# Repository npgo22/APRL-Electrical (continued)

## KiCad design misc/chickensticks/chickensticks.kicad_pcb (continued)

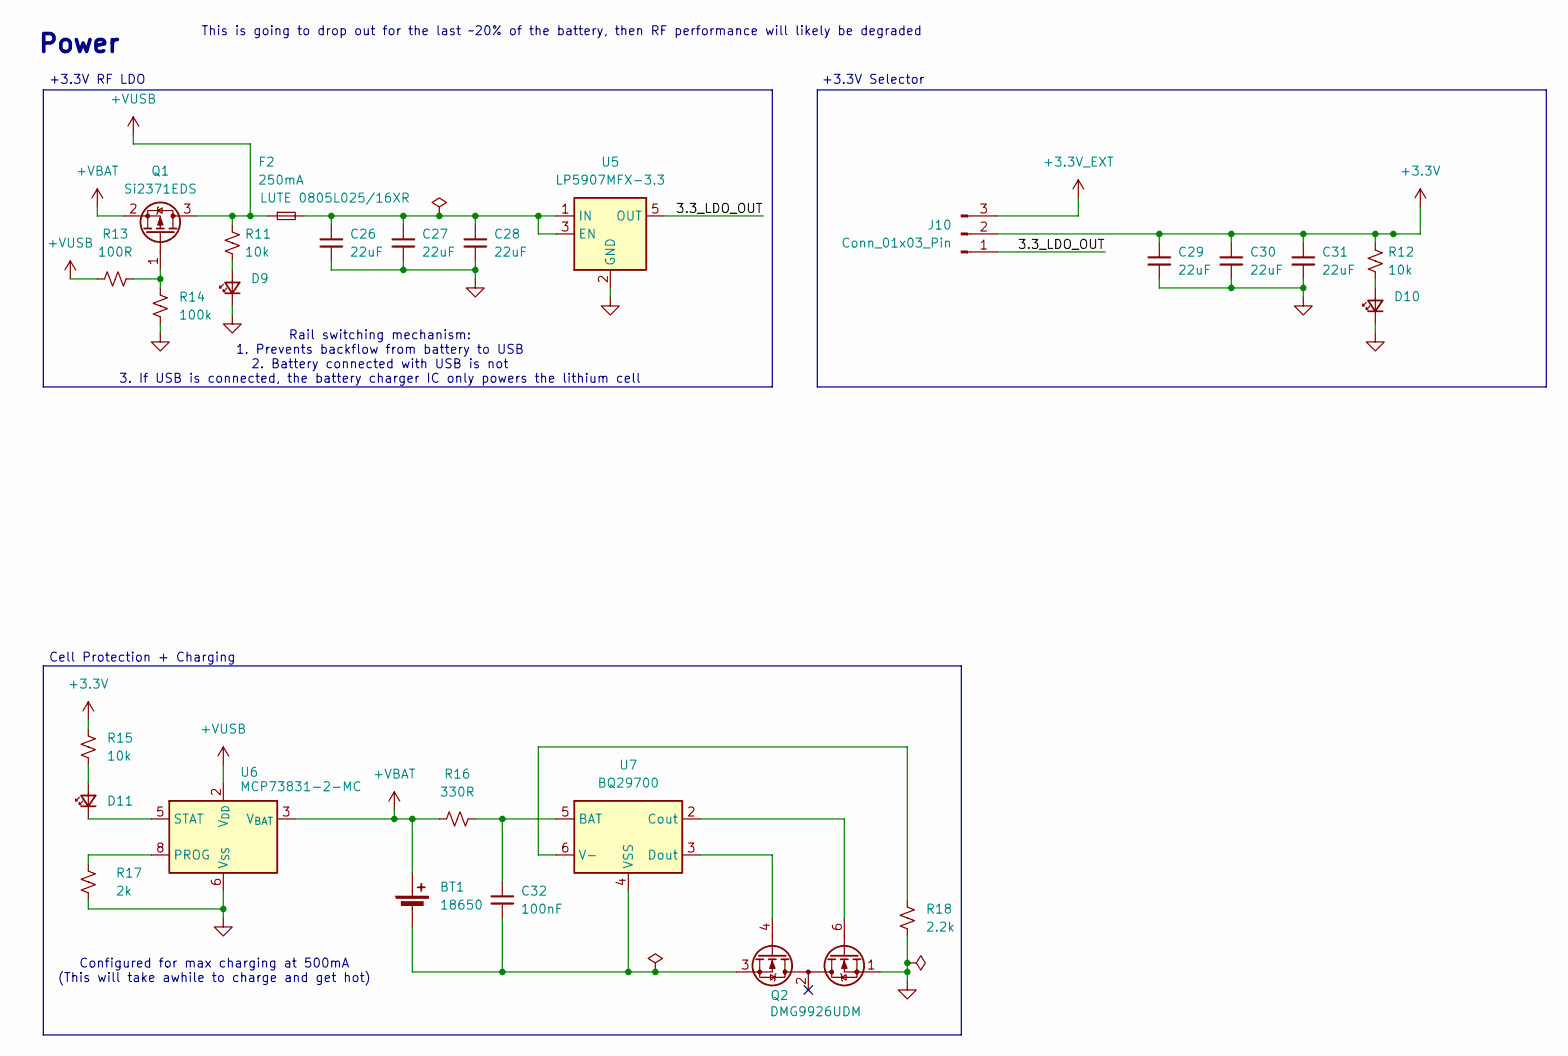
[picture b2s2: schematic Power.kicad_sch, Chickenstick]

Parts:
BT1: 18650; BatteryHolder_Keystone_1042_1x18650
C26, C27, C28, C29, C30, C31: 22uF; C_0805
C32: 100nF; C_0603
D9, D10, D11: LED_Small; LED_0603
F2: 250mA; Fuse_0805_2012Metric
J10: Conn_01x03_Pin; PinHeader_1x03_P2.54mm_Vertical
Q1: Si2371EDS; SOT-23
Q2: DMG9926UDM; SOT-23-6
R11, R12, R15: 10k; R_0603
R13: 100R; R_0603
R14: 100k; R_0603
R16: 330R; R_0603
R17: 2k; R_0603
R18: 2.2k; R_0603
U5: LP5907MFX-3.3; SOT-23-5
U6: MCP73831-2-MC; DFN-8-1EP_3x2mm_P0.5mm_EP1.7x1.4mm
U7: BQ29700; WSON-6_1.5x1.5mm_P0.5mm

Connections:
+3.3V: C29.1, C30.1, C31.1, J10.2, R12.1, R15.2; also elsewhere on the board
+3.3V_EXT: J10.3; also elsewhere on the board
+VUSB: F2.1, Q1.3 (D), R11.1, R13.1, U6.1 (V_{DD}), U6.2 (V_{DD}); also elsewhere on the board
/Power/3.3_LDO_OUT: J10.1, U5.5 (OUT)
unnamed: BT1.2 (-), C32.2, Q2.3 (S2), U7.4 (VSS)
unnamed: D9.2 (A), R11.2
unnamed: D10.2 (A), R12.2
unnamed: D11.2 (A), R15.1
unnamed: D11.1 (K), U6.5 (STAT)
unnamed: Q1.1 (G), R13.2, R14.1
unnamed: Q2.6 (G1), U7.2 (Cout)
unnamed: Q2.4 (G2), U7.3 (Dout)
unnamed: C26.1, C27.1, C28.1, F2.2, U5.1 (IN), U5.3 (EN)
unnamed: R17.1, U6.8 (PROG)
unnamed: C32.1, R16.2, U7.5 (BAT)
unnamed: R18.1, U7.6 (V-)

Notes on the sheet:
Configured for max charging at 500mA (This will take awhile to charge and get hot)
This is going to drop out for the last ~20% of the battery, then RF performance will likely be degraded
Power
Rail switching mechanism: 1. Prevents backflow from battery to USB 2. Battery connected with USB is not 3. If USB is connected, the battery charger IC only powers the lithium cell
+3.3V RF LDO
Cell Protection + Charging
+3.3V Selector

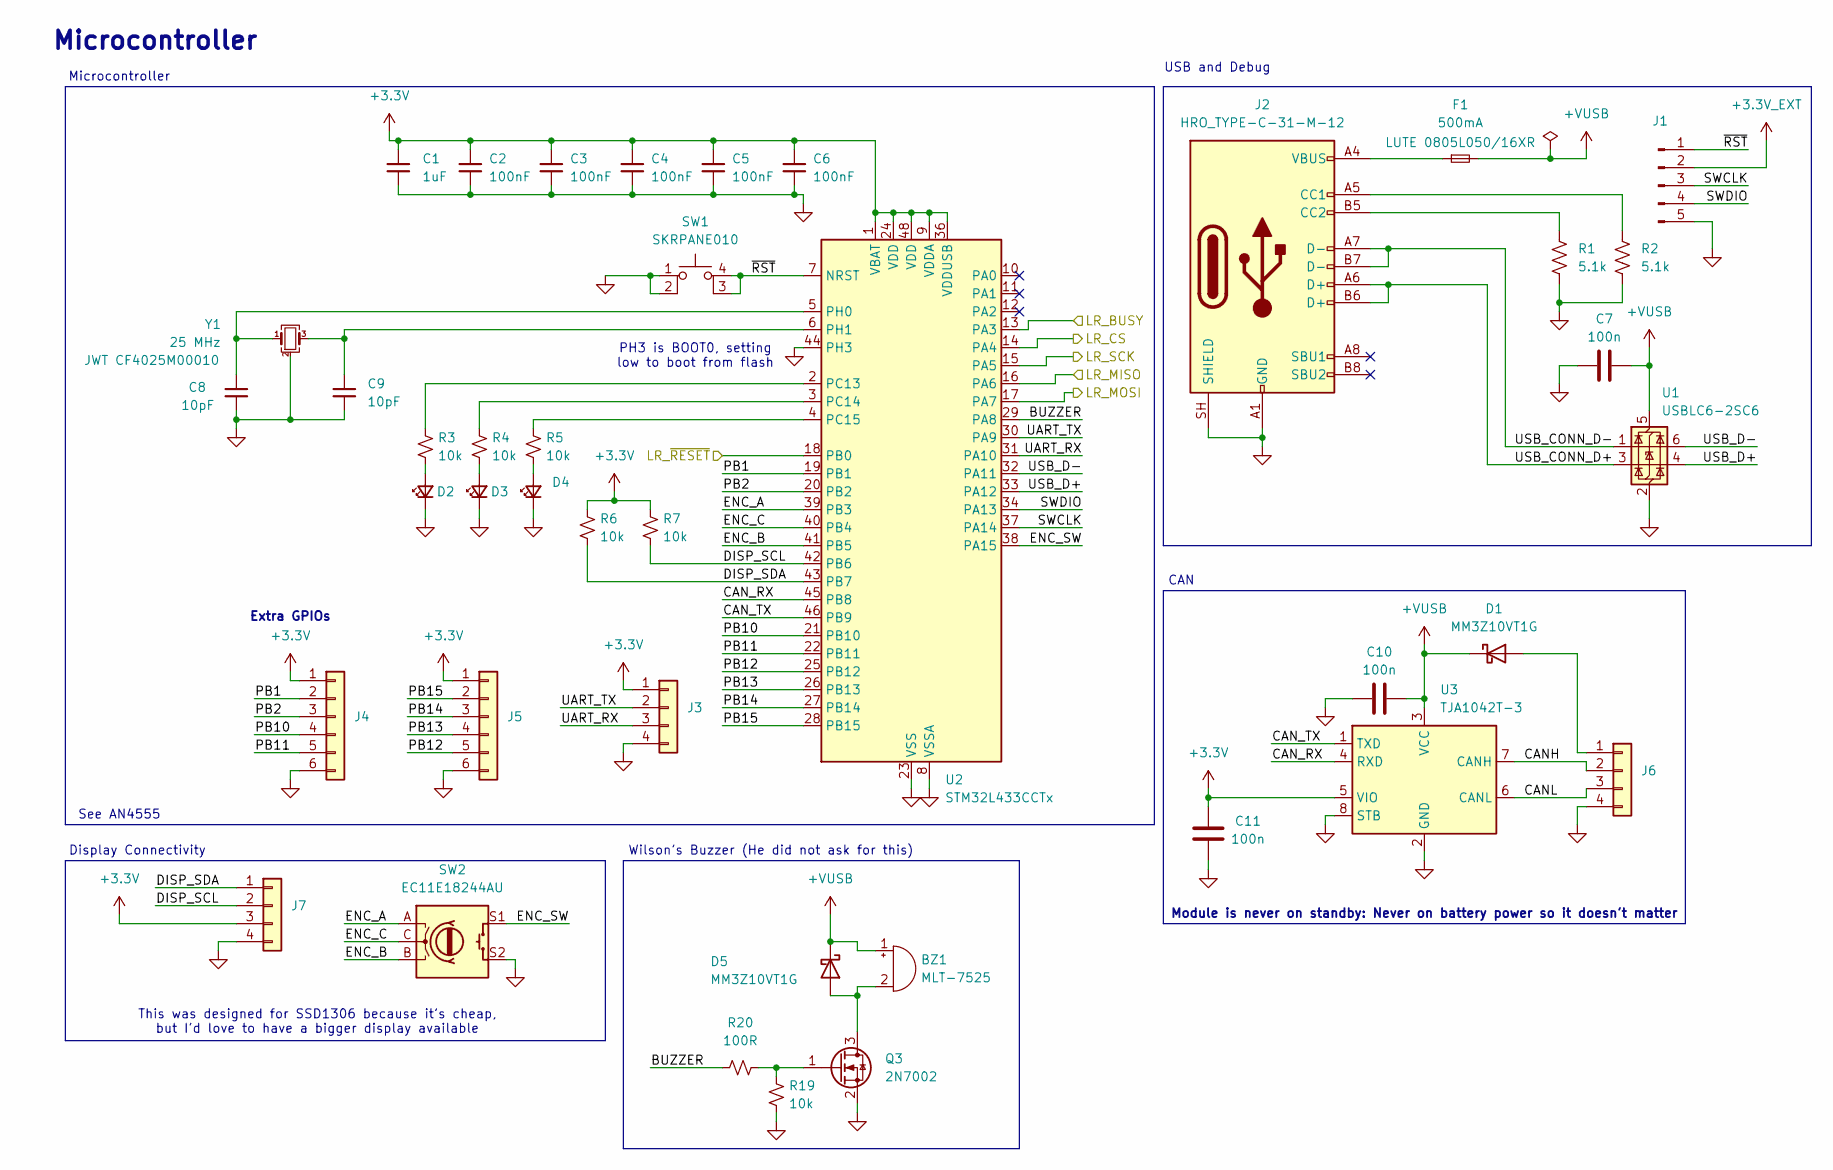
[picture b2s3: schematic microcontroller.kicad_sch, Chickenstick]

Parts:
BZ1: MLT-7525
C1: 1uF; C_0805
C2, C3, C4, C5, C6: 100nF; C_0603
C7, C10, C11: 100n; C_0603
C8, C9: 10pF; C_0603
D1, D5: MM3Z10VT1G; SOD-323
D2, D3, D4: LED_Small; LED_0603
F1: 500mA; Fuse_0805_2012Metric
J1: Conn_01x05_Pin; PinHeader_1x05_P2.54mm_Vertical
J2: HRO_TYPE-C-31-M-12; USB_C_Receptacle_HRO_TYPE-C-31-M-12
J3, J6, J7: Conn_01x04; PinHeader_1x04_P2.54mm_Vertical
J4, J5: Conn_01x06; PinHeader_1x06_P2.54mm_Vertical
Q3: 2N7002; SOT-23
R1, R2: 5.1k; R_0603
R3, R4, R5, R6, R7, R19: 10k; R_0603
R20: 100R; R_0603
SW1: SKRPANE010
SW2: EC11E18244AU; RotaryEncoder_Alps_EC11E-Switch_Vertical_H20mm_MountingHoles
U1: USBLC6-2SC6; SOT-23-6
U2: STM32L433CCTx; LQFP-48_7x7mm_P0.5mm
U3: TJA1042T-3; SOIC-8_3.9x4.9mm_P1.27mm
Y1: 25 MHz; 3225-4P-L

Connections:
+3.3V: C1.1, C2.1, C3.1, C4.1, C5.1, C6.1, C11.2, J3.1, J4.1, J5.1, J7.3, R6.1, R7.1, U2.1 (VBAT), U2.9 (VDDA), U2.24 (VDD), U2.36 (VDDUSB), U2.48 (VDD), U3.5 (VIO); also elsewhere on the board
+3.3V_EXT: J1.2; also elsewhere on the board
+VUSB: BZ1.1 (+), C7.2, C10.2, D1.1 (K), D5.1 (K), F1.2, U1.5 (VBUS), U3.3 (VCC); also elsewhere on the board
/LoRa Transceiver/LR_BUSY: U2.13 (PA3); also elsewhere on the board
/LoRa Transceiver/LR_CS: U2.14 (PA4); also elsewhere on the board
/LoRa Transceiver/LR_MISO: U2.16 (PA6); also elsewhere on the board
/LoRa Transceiver/LR_MOSI: U2.17 (PA7); also elsewhere on the board
/LoRa Transceiver/LR_SCK: U2.15 (PA5); also elsewhere on the board
/LoRa Transceiver/LR_~RESET: U2.18 (PB0); also elsewhere on the board
/Microcontroller/BUZZER: R20.1, U2.29 (PA8)
/Microcontroller/CANH: J6.2, U3.7 (CANH)
/Microcontroller/CANL: J6.3, U3.6 (CANL)
/Microcontroller/CAN_RX: U2.45 (PB8), U3.4 (RXD)
/Microcontroller/CAN_TX: U2.46 (PB9), U3.1 (TXD)
/Microcontroller/DISP_SCL: J7.2, R7.2, U2.42 (PB6)
/Microcontroller/DISP_SDA: J7.1, R6.2, U2.43 (PB7)
/Microcontroller/ENC_A: SW2.A, U2.39 (PB3)
/Microcontroller/ENC_B: SW2.B, U2.41 (PB5)
/Microcontroller/ENC_C: SW2.C, U2.40 (PB4)
/Microcontroller/ENC_SW: SW2.S1, U2.38 (PA15)
/Microcontroller/PB1: J4.2, U2.19 (PB1)
/Microcontroller/PB2: J4.3, U2.20 (PB2)
/Microcontroller/PB10: J4.4, U2.21 (PB10)
/Microcontroller/PB11: J4.5, U2.22 (PB11)
/Microcontroller/PB12: J5.5, U2.25 (PB12)
/Microcontroller/PB13: J5.4, U2.26 (PB13)
/Microcontroller/PB14: J5.3, U2.27 (PB14)
/Microcontroller/PB15: J5.2, U2.28 (PB15)
/Microcontroller/SWCLK: J1.3, U2.37 (PA14)
/Microcontroller/SWDIO: J1.4, U2.34 (PA13)
/Microcontroller/UART_RX: J3.3, U2.31 (PA10)
/Microcontroller/UART_TX: J3.2, U2.30 (PA9)
/Microcontroller/USB_CONN_D+: J2.A6 (D+), J2.B6 (D+), U1.3 (I/O2)
/Microcontroller/USB_CONN_D-: J2.A7 (D-), J2.B7 (D-), U1.1 (I/O1)
/Microcontroller/USB_D+: U1.4 (I/O2), U2.33 (PA12)
/Microcontroller/USB_D-: U1.6 (I/O1), U2.32 (PA11)
/Microcontroller/~RST: J1.1, SW1.3 (K), SW1.4 (A), U2.7 (NRST)
unnamed: BZ1.2 (-), D5.2 (A), Q3.3 (D)
unnamed: D1.2 (A), J6.1
unnamed: D2.2 (A), R3.2
unnamed: D3.2 (A), R4.2
unnamed: D4.2 (A), R5.2
unnamed: F1.1, J2.A4 (VBUS), J2.A9 (VBUS), J2.B4 (VBUS), J2.B9 (VBUS)
unnamed: J2.A5 (CC1), R2.1
unnamed: J2.B5 (CC2), R1.1
unnamed: Q3.1 (G), R19.1, R20.2
unnamed: R3.1, U2.2 (PC13)
unnamed: R4.1, U2.3 (PC14)
unnamed: R5.1, U2.4 (PC15)
unnamed: C8.1, U2.5 (PH0), Y1.1
unnamed: C9.1, U2.6 (PH1), Y1.3

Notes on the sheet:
Microcontroller
Extra GPIOs
Module is never on standby: Never on battery power so it doesn't matter
See AN4555
Display Connectivity
Wilson's Buzzer (He did not ask for this)
This was designed for SSD1306 because it's cheap, but I'd love to have a bigger display available
CAN
PH3 is BOOT0, setting low to boot from flash
USB and Debug

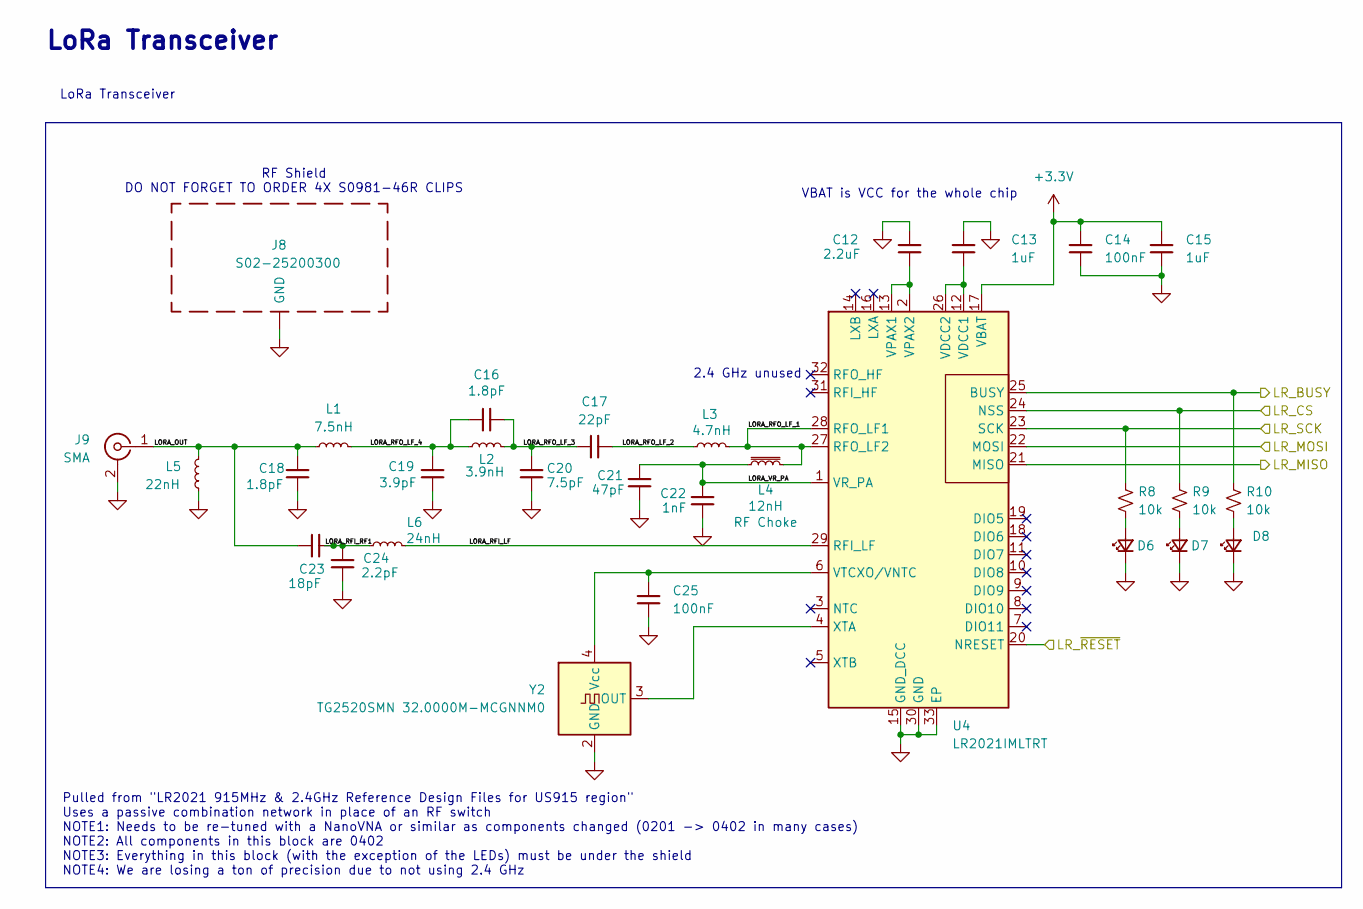
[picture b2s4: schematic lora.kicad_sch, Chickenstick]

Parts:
C12: 2.2uF; C_0805
C13, C15: 1uF; C_0805
C14, C25: 100nF; C_0603
C16, C18: 1.8pF; C_0402
C17: 22pF; C_0402
C19: 3.9pF; C_0402
C20: 7.5pF; C_0402
C21: 47pF; C_0402
C22: 1nF; C_0402
C23: 18pF; C_0402
C24: 2.2pF; C_0402
D6, D7, D8: LED_Small; LED_0603
J8: S02-25200300; S02-25200300-Outline
J9: SMA; SMA_Amphenol_132203-12_Horizontal
L1: 7.5nH; L_0402
L2: 3.9nH; L_0402
L3: 4.7nH; L_0402
L4: 12nH; L_0402
L5: 22nH; L_0402
L6: 24nH; L_0402
R8, R9, R10: 10k; R_0603
U4: LR2021IMLTRT; QFN-32_EP_5.8x5.8_Pitch0.5mm
Y2: TG2520SMN 32.0000M-MCGNNM0; Oscillator_SMD_SeikoEpson_TG2520SMN-xxx-xxxxxx-4Pin_2.5x2.0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

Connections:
+3.3V: C14.1, C15.1, U4.17 (VBAT); also elsewhere on the board
/LoRa Transceiver/LORA_OUT: C18.2, C23.1, J9.1 (In), L1.1, L5.2
/LoRa Transceiver/LORA_RFI_LF: L6.2, U4.29 (RFI_LF)
/LoRa Transceiver/LORA_RFI_RF1: C23.2, C24.1, L6.1
/LoRa Transceiver/LORA_RFO_LF_1: L3.2, L4.2, U4.27 (RFO_LF2), U4.28 (RFO_LF1)
/LoRa Transceiver/LORA_RFO_LF_2: C17.1, L3.1
/LoRa Transceiver/LORA_RFO_LF_3: C16.1, C17.2, C20.2, L2.2
/LoRa Transceiver/LORA_RFO_LF_4: C16.2, C19.2, L1.2, L2.1
/LoRa Transceiver/LORA_VR_PA: C21.2, C22.2, L4.1, U4.1 (VR_PA)
/LoRa Transceiver/LR_BUSY: R10.1, U4.25 (BUSY); also elsewhere on the board
/LoRa Transceiver/LR_CS: R9.1, U4.24 (NSS); also elsewhere on the board
/LoRa Transceiver/LR_MISO: U4.21 (MISO); also elsewhere on the board
/LoRa Transceiver/LR_MOSI: U4.22 (MOSI); also elsewhere on the board
/LoRa Transceiver/LR_SCK: R8.1, U4.23 (SCK); also elsewhere on the board
/LoRa Transceiver/LR_~RESET: U4.20 (NRESET); also elsewhere on the board
unnamed: D6.2 (A), R8.2
unnamed: D7.2 (A), R9.2
unnamed: D8.2 (A), R10.2
unnamed: C13.2, U4.12 (VDCC1), U4.26 (VDCC2)
unnamed: C12.1, U4.2 (VPAX2), U4.13 (VPAX1)
unnamed: C25.1, U4.6 (VTCXO/VNTC), Y2.4 (Vcc)
unnamed: U4.4 (XTA), Y2.3 (OUT)

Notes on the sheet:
RF Shield DO NOT FORGET TO ORDER 4X S0981-46R CLIPS
2.4 GHz unused
Pulled from "LR2021 915MHz & 2.4GHz Reference Design Files for US915 region" Uses a passive combination network in place of an RF switch NOTE1: Needs to be re-tuned with a NanoVNA or similar as components changed (0201 -> 0402 in many cases) NOTE2: All components in this block are 0402 NOTE3: Every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
VBAT is VCC for the whole chip
LoRa Transceiver

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
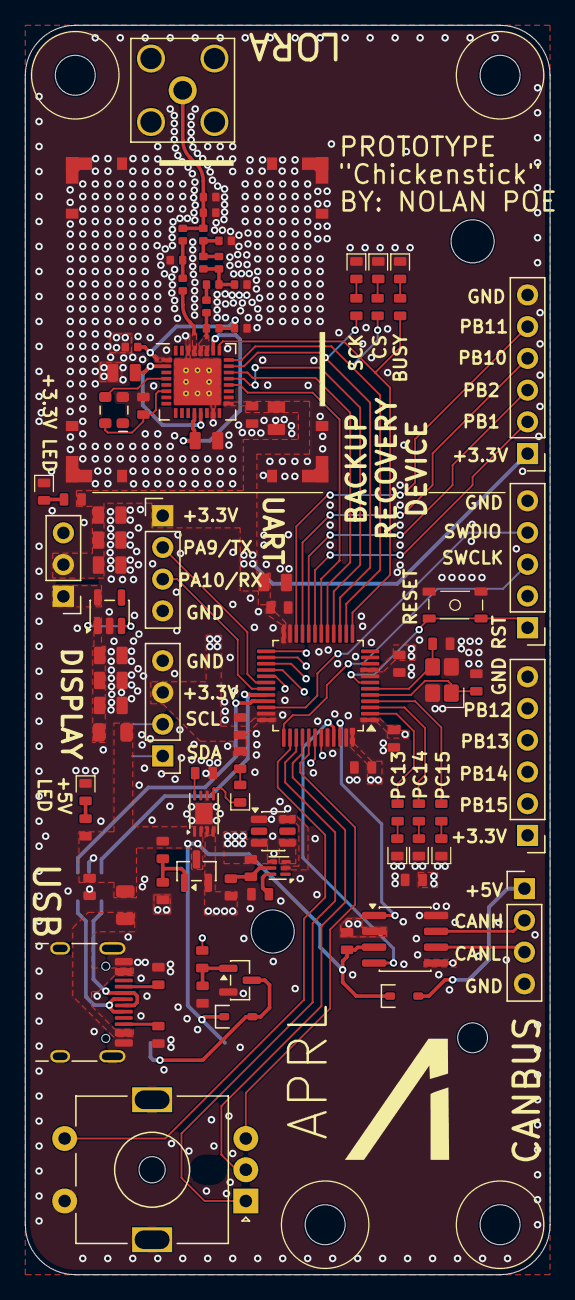
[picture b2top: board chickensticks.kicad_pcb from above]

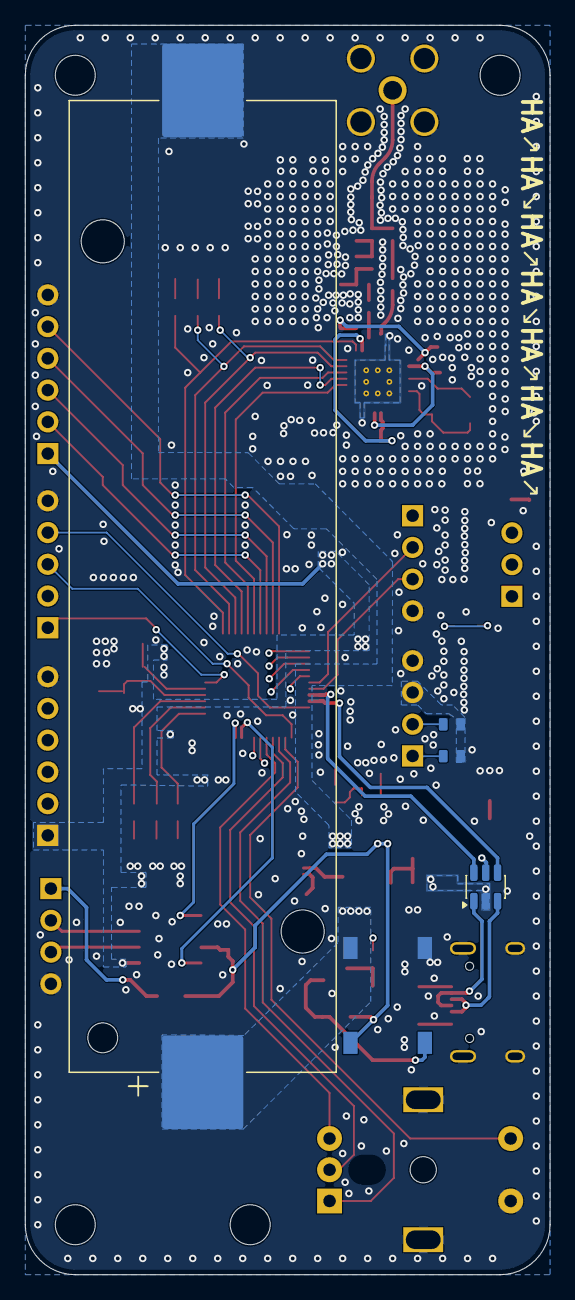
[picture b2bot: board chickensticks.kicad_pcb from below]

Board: 4 copper layers, 42.0 x 100.0 mm, 101 parts (5 on the bottom side), 81 nets.

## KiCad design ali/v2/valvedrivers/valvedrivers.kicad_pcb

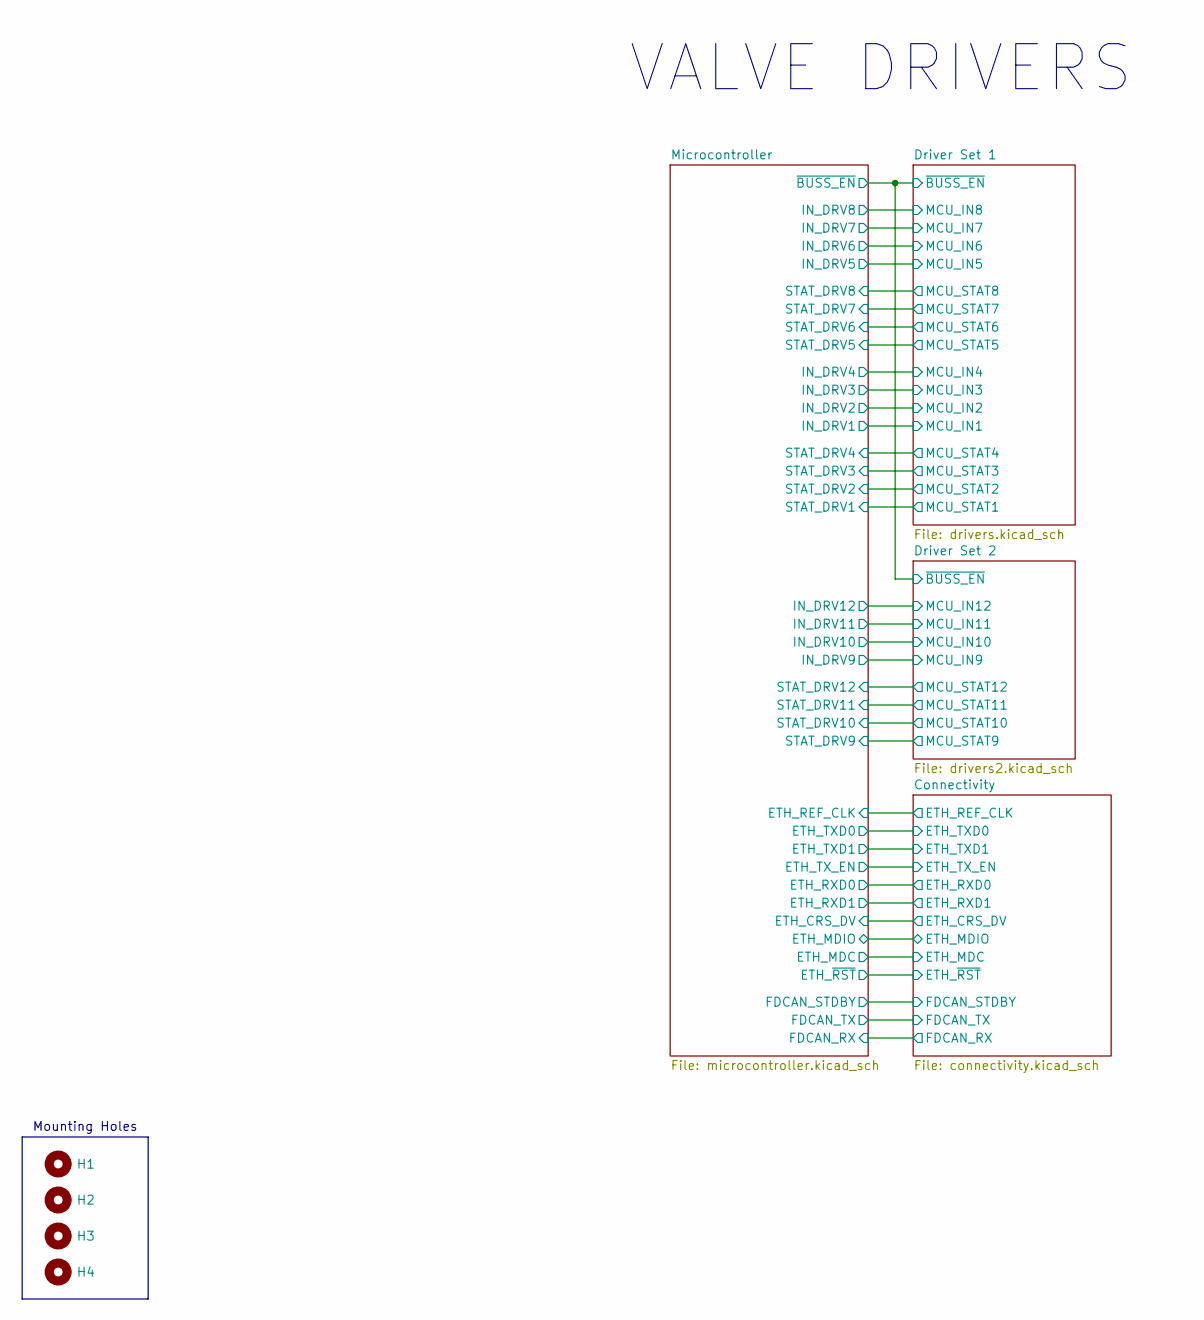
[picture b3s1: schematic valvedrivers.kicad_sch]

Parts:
H1, H2, H3, H4: MountingHole; MountingHole_3.2mm_M3

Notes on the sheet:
VALVE DRIVERS
Mounting Holes

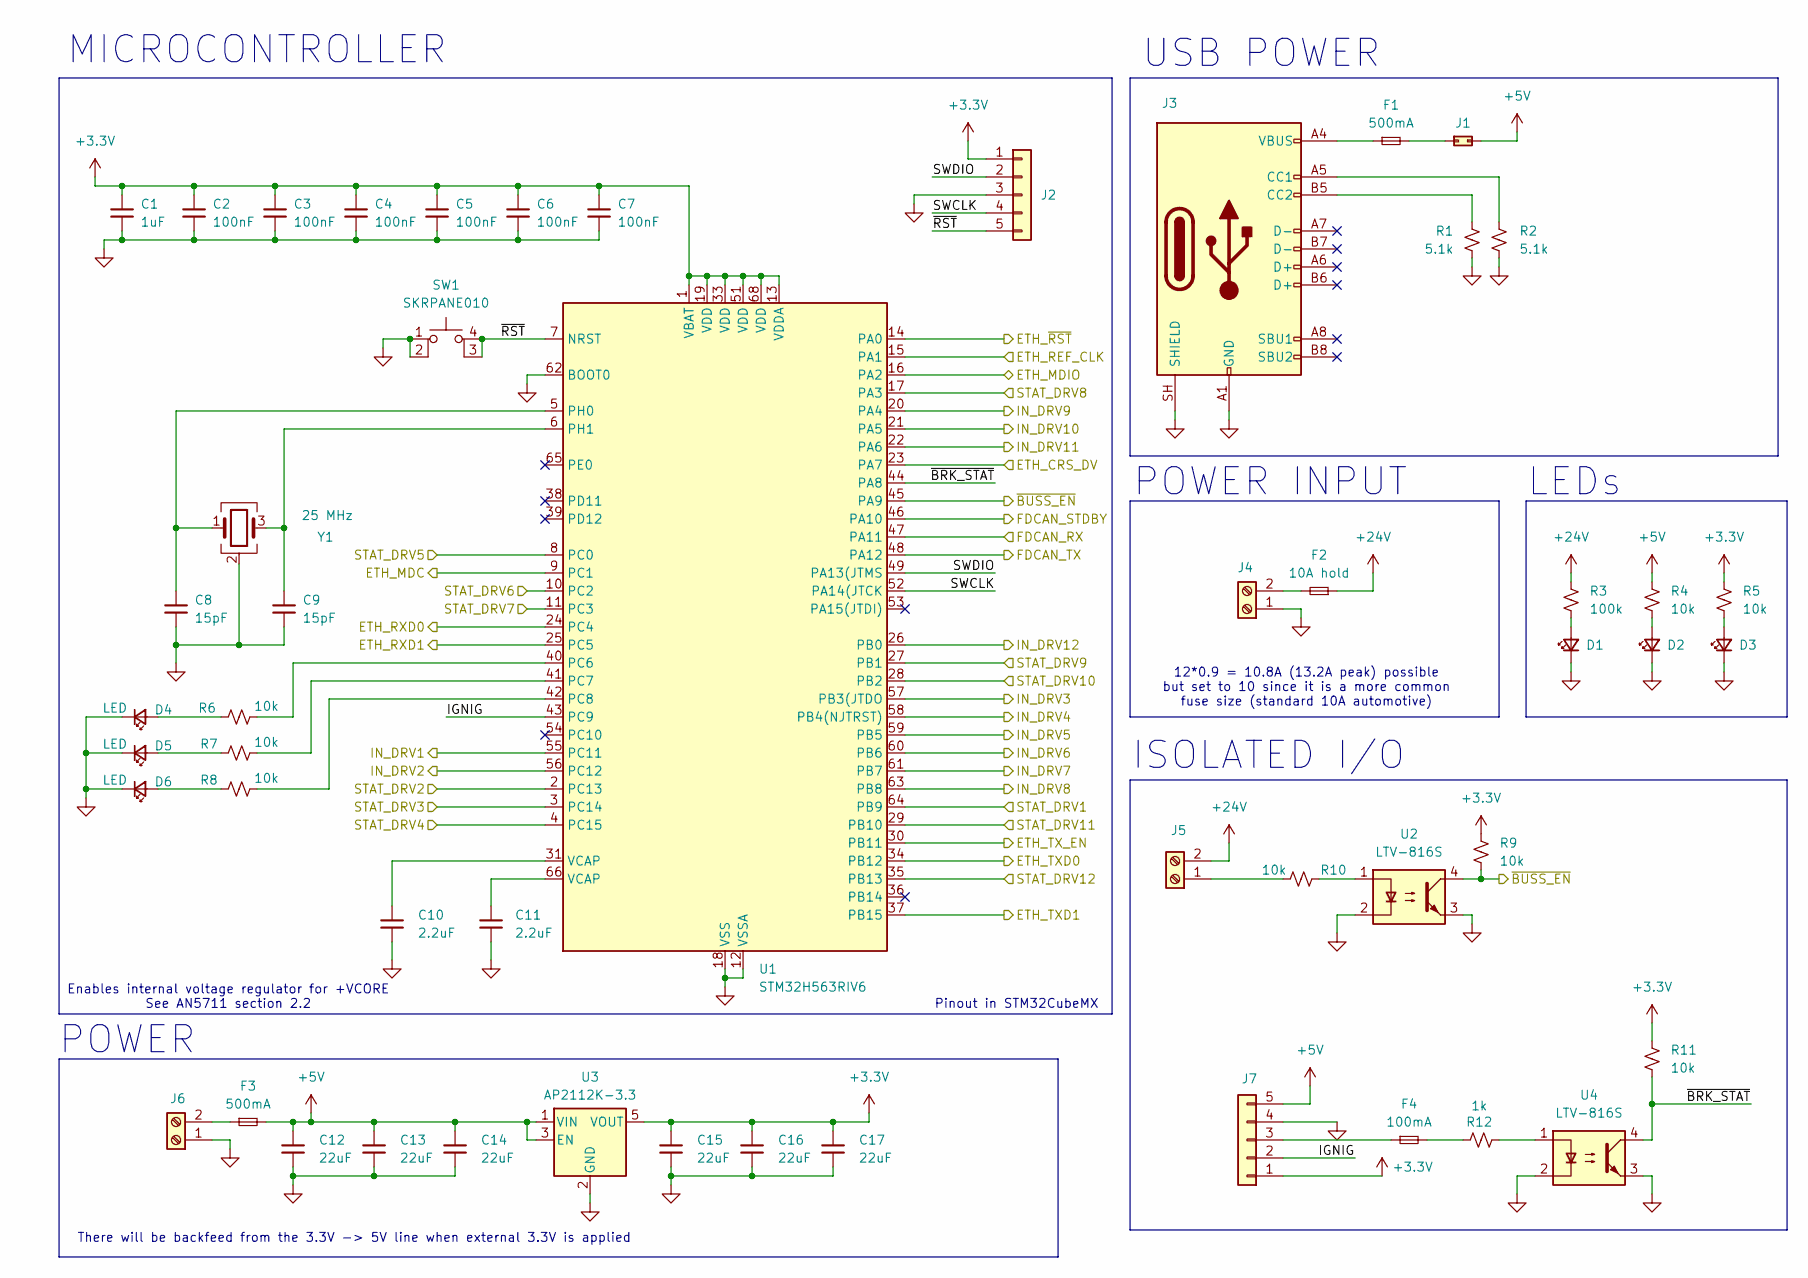
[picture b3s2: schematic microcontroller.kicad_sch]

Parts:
C1: 1uF; C_0603; MPN GRM188D72A105KE01
C2, C3, C4, C5, C6, C7: 100nF; C_0603; MPN GRM188R72A104KA35
C8, C9: 15pF; C_0603; MPN GRM1885C2E150FW07
C10, C11: 2.2uF; C_0603; MPN GRM188R71A225KE15
C12, C13, C14, C15, C16, C17: 22uF; C_0805; MPN GRM21BZ71A226ME15
D1, D2, D3, D4, D5, D6: LED; LED_0603
F1, F3: 500mA; Fuse_0805_2012Metric; MPN 0805L050WR
F2: 10A hold; FuseHolder_Blade_ATO_Littelfuse_FLR_178.6165; MPN 178.6165.0001
F4: 100mA; Fuse_0805_2012Metric; MPN 1206L010/60WR
J1: Conn_02x01; PinHeader_1x02_P2.54mm_Vertical
J2, J7: Conn_01x05; Molex_CLIK-Mate_503159-0501_1x05-1MP_P1.50mm_Vertical; MPN 503159-0501
J3: USB_C_Receptacle_USB2.0_16P; USB_C_Receptacle_G-Switch_GT-USB-7051x; MPN GT-USB-7051A
J4, J5, J6: Screw_Terminal_01x02; PhoenixContact_MSTBV_2,5_2-GF-5,08_1x02_P5.08mm_Vertical_Th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; MPN MSTBV 2,5/ 2-GF-5,08
R1, R2: 5.1k; R_0603; MPN RC0603FR-075K1L
R3: 100k; R_0603; MPN RC0603FR-07100KL
R4, R5, R6, R7, R8, R9, R10, R11: 10k; R_0603; MPN RC0603FR-0710KL
R12: 1k; R_0603; MPN RC0603FR-071KL
SW1: SKRPANE010; MPN SKRPANE010
U1: STM32H563RIV6; QFN-68-1EP_8x8mm_P0.4mm_EP6.4x6.4mm; MPN STM32H563RIV6
U2, U4: LTV-816S; 4-SMD; MPN LTV-816S-TA1-C
U3: AP2112K-3.3; SOT-23-5; MPN AP2112K-3.3TRG1
Y1: 25 MHz; 3225-4P-L; MPN X1E0000210139

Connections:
+3.3V: C1.1, C2.1, C3.1, C4.1, C5.1, C6.1, C7.1, C15.1, C16.1, C17.1, J2.1, J7.1, R5.1, R9.1, R11.1, U1.1 (VBAT), U1.13 (VDDA), U1.19 (VDD), U1.33 (VDD), U1.51 (VDD), U1.68 (VDD), U3.5 (VOUT); also elsewhere on the board
+5V: C12.1, C13.1, C14.1, F3.2, J1.2, J7.5, R4.1, U3.1 (VIN), U3.3 (EN); also elsewhere on the board
+24V: F2.1, J5.2, R3.1; also elsewhere on the board
/Connectivity/ETH_CRS_DV: U1.23 (PA7); also elsewhere on the board
/Connectivity/ETH_MDC: U1.9 (PC1); also elsewhere on the board
/Connectivity/ETH_MDIO: U1.16 (PA2); also elsewhere on the board
/Connectivity/ETH_REF_CLK: U1.15 (PA1); also elsewhere on the board
/Connectivity/ETH_RXD0: U1.24 (PC4); also elsewhere on the board
/Connectivity/ETH_RXD1: U1.25 (PC5); also elsewhere on the board
/Connectivity/ETH_TXD0: U1.34 (PB12); also elsewhere on the board
/Connectivity/ETH_TXD1: U1.37 (PB15); also elsewhere on the board
/Connectivity/ETH_TX_EN: U1.30 (PB11); also elsewhere on the board
/Connectivity/ETH_~RST: U1.14 (PA0); also elsewhere on the board
/Connectivity/FDCAN_RX: U1.47 (PA11); also elsewhere on the board
/Connectivity/FDCAN_STDBY: U1.46 (PA10); also elsewhere on the board
/Connectivity/FDCAN_TX: U1.48 (PA12); also elsewhere on the board
/Driver Set 1/MCU_IN1: U1.55 (PC11); also elsewhere on the board
/Driver Set 1/MCU_IN2: U1.56 (PC12); also elsewhere on the board
/Driver Set 1/MCU_IN3: U1.57 (PB3(JTDO); also elsewhere on the board
/Driver Set 1/MCU_IN4: U1.58 (PB4(NJTRST)); also elsewhere on the board
/Driver Set 1/MCU_IN5: U1.59 (PB5); also elsewhere on the board
/Driver Set 1/MCU_IN6: U1.60 (PB6); also elsewhere on the board
/Driver Set 1/MCU_IN7: U1.61 (PB7); also elsewhere on the board
/Driver Set 1/MCU_IN8: U1.63 (PB8); also elsewhere on the board
/Driver Set 1/MCU_STAT1: U1.64 (PB9); also elsewhere on the board
/Driver Set 1/MCU_STAT2: U1.2 (PC13); also elsewhere on the board
/Driver Set 1/MCU_STAT3: U1.3 (PC14); also elsewhere on the board
/Driver Set 1/MCU_STAT4: U1.4 (PC15); also elsewhere on the board
/Driver Set 1/MCU_STAT5: U1.8 (PC0); also elsewhere on the board
/Driver Set 1/MCU_STAT6: U1.10 (PC2); also elsewhere on the board
/Driver Set 1/MCU_STAT7: U1.11 (PC3); also elsewhere on the board
/Driver Set 1/MCU_STAT8: U1.17 (PA3); also elsewhere on the board
/Driver Set 1/~BUSS_EN: R9.2, U1.45 (PA9), U2.4; also elsewhere on the board
/Driver Set 2/MCU_IN9: U1.20 (PA4); also elsewhere on the board
/Driver Set 2/MCU_IN10: U1.21 (PA5); also elsewhere on the board
/Driver Set 2/MCU_IN11: U1.22 (PA6); also elsewhere on the board
/Driver Set 2/MCU_IN12: U1.26 (PB0); also elsewhere on the board
/Driver Set 2/MCU_STAT9: U1.27 (PB1); also elsewhere on the board
/Driver Set 2/MCU_STAT10: U1.28 (PB2); also elsewhere on the board
/Driver Set 2/MCU_STAT11: U1.29 (PB10); also elsewhere on the board
/Driver Set 2/MCU_STAT12: U1.35 (PB13); also elsewhere on the board
/Microcontroller/IGNIG: J7.2, U1.43 (PC9)
/Microcontroller/SWCLK: J2.4, U1.52 (PA14(JTCK)
/Microcontroller/SWDIO: J2.2, U1.49 (PA13(JTMS)
/Microcontroller/~BRK_STAT: R11.2, U1.44 (PA8), U4.4
/Microcontroller/~RST: J2.5, SW1.3 (K), SW1.4 (A), U1.7 (NRST)
GND: C1.2, C2.2, C3.2, C4.2, C5.2, C6.2, C7.2, C8.2, C9.2, C10.2, C11.2, C12.2, C13.2, C14.2, C15.2, C16.2, C17.2, D1.1 (K), D2.1 (K), D3.1 (K), D4.1 (K), D5.1 (K), D6.1 (K), J2.3, J3.A1 (GND), J3.A12 (GND), J3.B1 (GND), J3.B12 (GND), J3.SH (SHIELD), J4.1, J6.1, J7.4, R1.1, R2.2, SW1.1, SW1.2, U1.12 (VSSA), U1.18 (VSS), U1.32 (VSS), U1.50 (VSS), U1.62 (BOOT0), U1.67 (VSS), U1.69 (VSS), U2.2, U2.3, U3.2 (GND), U4.2, U4.3, Y1.2 (G), Y1.4 (G); also elsewhere on the board
unnamed: C10.1, U1.31 (VCAP)
unnamed: C11.1, U1.66 (VCAP)
unnamed: D1.2 (A), R3.2
unnamed: D2.2 (A), R4.2
unnamed: D3.2 (A), R5.2
unnamed: D4.2 (A), R6.1
unnamed: D5.2 (A), R7.1
unnamed: D6.2 (A), R8.1
unnamed: F1.1, J3.A4 (VBUS), J3.A9 (VBUS), J3.B4 (VBUS), J3.B9 (VBUS)
unnamed: F4.2, R12.1
unnamed: F1.2, J1.1
unnamed: J3.A5 (CC1), R2.1
unnamed: J3.B5 (CC2), R1.2
unnamed: F2.2, J4.2
unnamed: J5.1, R10.1
unnamed: F3.1, J6.2
unnamed: F4.1, J7.3
unnamed: R10.2, U2.1
unnamed: R12.2, U4.1
unnamed: R6.2, U1.40 (PC6)
unnamed: R7.2, U1.41 (PC7)
unnamed: R8.2, U1.42 (PC8)
unnamed: C8.1, U1.5 (PH0), Y1.1
unnamed: C9.1, U1.6 (PH1), Y1.3

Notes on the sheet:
Enables internal voltage regulator for +VCORE See AN5711 section 2.2
MICROCONTROLLER
There will be backfeed from the 3.3V -> 5V line when external 3.3V is applied
USB POWER
POWER
ISOLATED I/O
Pinout in STM32CubeMX
POWER INPUT
12*0.9 = 10.8A (13.2A peak) possible but set to 10 since it is a more common fuse size (standard 10A automotive)
LEDs

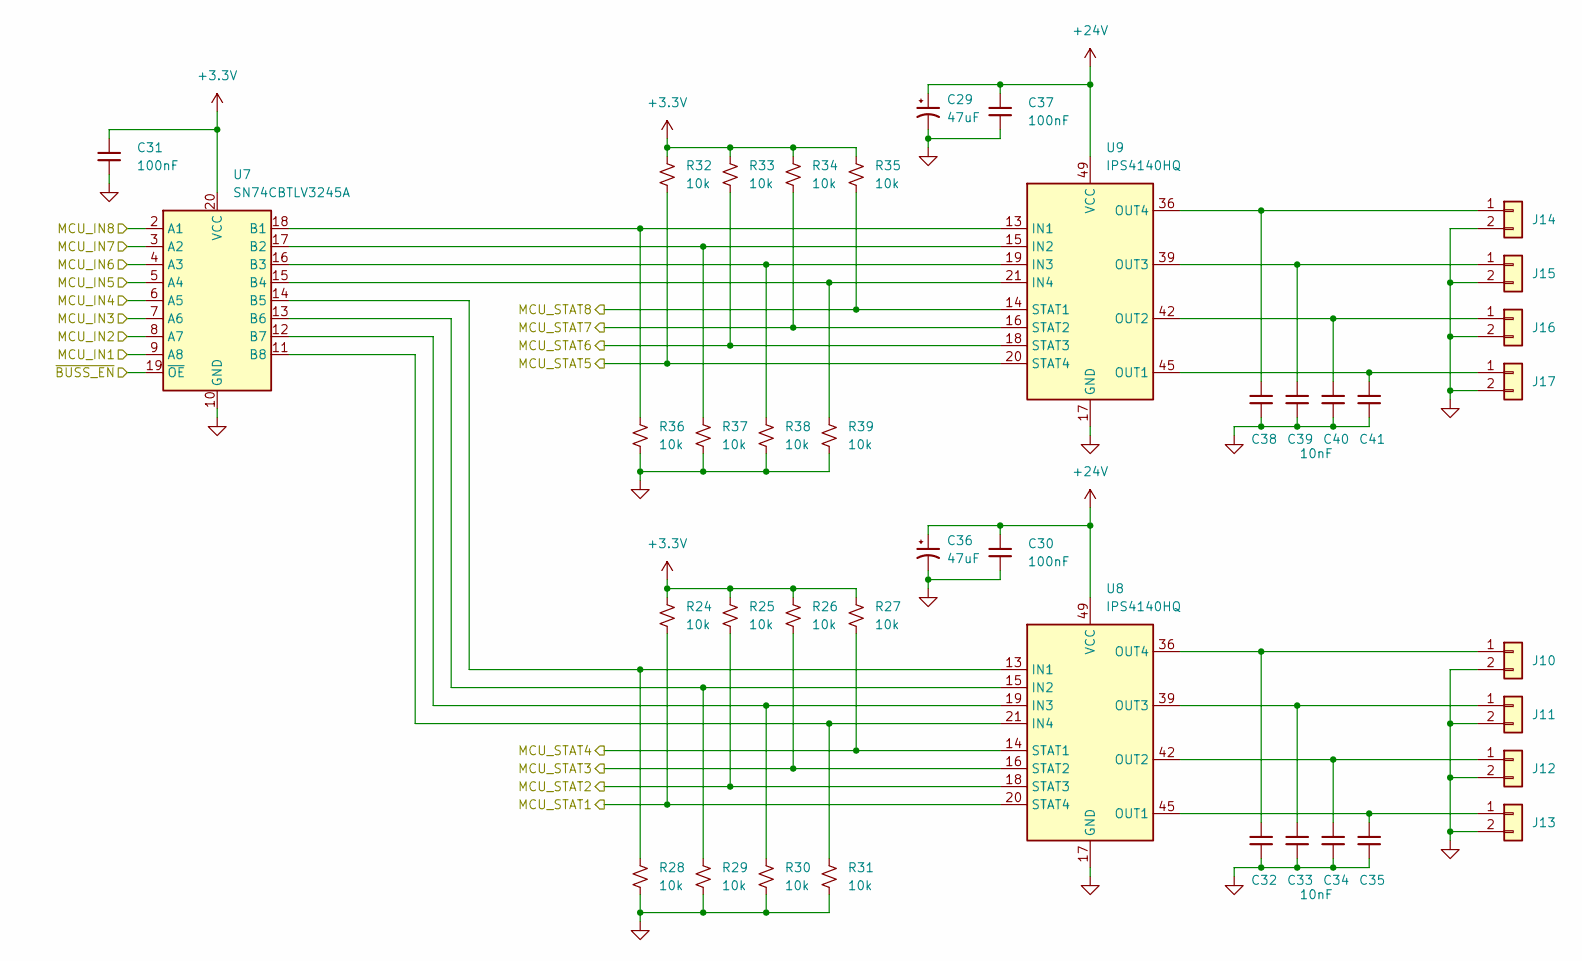
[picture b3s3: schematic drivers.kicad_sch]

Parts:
C29, C36: 47uF; KEMET MU VIB; MPN A767KS476M1JLAE036
C30, C31, C37: 100nF; C_0603; MPN GRM188R72A104KA35
C32, C33, C34, C35, C38, C39, C40, C41: 10nF; C_0603; MPN GRM1885C1H103JA01
J10, J11, J12, J13, J14, J15, J16, J17: Conn_01x02; Molex_CLIK-Mate_503159-0201_1x02-1MP_P1.50mm_Vertical; MPN 503159-0201
R24, R25, R26, R27, R28, R29, R30, R31, R32, R33, R34, R35, R36, R37, R38, R39: 10k; R_0603; MPN RC0603FR-0710KL
U7: SN74CBTLV3245A; TSSOP-20_4.4x6.5mm_P0.65mm; MPN SN74CBTLV3245APWR
U8, U9: IPS4140HQ; QFN-48_EP_9.01x7.01_Pitch0.5mm; MPN IPS4140HQ

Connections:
+3.3V: C31.1, R24.1, R25.1, R26.1, R27.1, R32.1, R33.1, R34.1, R35.1, U7.20 (VCC); also elsewhere on the board
+24V: C29.1, C30.1, C36.1, C37.1, U8.49 (VCC), U9.49 (VCC); also elsewhere on the board
/Driver Set 1/MCU_IN1: U7.9 (A8); also elsewhere on the board
/Driver Set 1/MCU_IN2: U7.8 (A7); also elsewhere on the board
/Driver Set 1/MCU_IN3: U7.7 (A6); also elsewhere on the board
/Driver Set 1/MCU_IN4: U7.6 (A5); also elsewhere on the board
/Driver Set 1/MCU_IN5: U7.5 (A4); also elsewhere on the board
/Driver Set 1/MCU_IN6: U7.4 (A3); also elsewhere on the board
/Driver Set 1/MCU_IN7: U7.3 (A2); also elsewhere on the board
/Driver Set 1/MCU_IN8: U7.2 (A1); also elsewhere on the board
/Driver Set 1/MCU_STAT1: R24.2, U8.20 (STAT4); also elsewhere on the board
/Driver Set 1/MCU_STAT2: R25.2, U8.18 (STAT3); also elsewhere on the board
/Driver Set 1/MCU_STAT3: R26.2, U8.16 (STAT2); also elsewhere on the board
/Driver Set 1/MCU_STAT4: R27.2, U8.14 (STAT1); also elsewhere on the board
/Driver Set 1/MCU_STAT5: R32.2, U9.20 (STAT4); also elsewhere on the board
/Driver Set 1/MCU_STAT6: R33.2, U9.18 (STAT3); also elsewhere on the board
/Driver Set 1/MCU_STAT7: R34.2, U9.16 (STAT2); also elsewhere on the board
/Driver Set 1/MCU_STAT8: R35.2, U9.14 (STAT1); also elsewhere on the board
/Driver Set 1/~BUSS_EN: U7.19 (~OE); also elsewhere on the board
GND: C29.2, C30.2, C31.2, C32.2, C33.2, C34.2, C35.2, C36.2, C37.2, C38.2, C39.2, C40.2, C41.2, J10.2, J11.2, J12.2, J13.2, J14.2, J15.2, J16.2, J17.2, R28.2, R29.2, R30.2, R31.2, R36.2, R37.2, R38.2, R39.2, U7.10 (GND), U8.17 (GND), U9.17 (GND); also elsewhere on the board
unnamed: C32.1, J10.1, U8.36 (OUT4), U8.37 (OUT4), U8.38 (OUT4)
unnamed: C33.1, J11.1, U8.39 (OUT3), U8.40 (OUT3), U8.41 (OUT3)
unnamed: C34.1, J12.1, U8.42 (OUT2), U8.43 (OUT2), U8.44 (OUT2)
unnamed: C35.1, J13.1, U8.45 (OUT1), U8.46 (OUT1), U8.47 (OUT1)
unnamed: C38.1, J14.1, U9.36 (OUT4), U9.37 (OUT4), U9.38 (OUT4)
unnamed: C39.1, J15.1, U9.39 (OUT3), U9.40 (OUT3), U9.41 (OUT3)
unnamed: C40.1, J16.1, U9.42 (OUT2), U9.43 (OUT2), U9.44 (OUT2)
unnamed: C41.1, J17.1, U9.45 (OUT1), U9.46 (OUT1), U9.47 (OUT1)
unnamed: R36.1, U7.18 (B1), U9.13 (IN1)
unnamed: R37.1, U7.17 (B2), U9.15 (IN2)
unnamed: R38.1, U7.16 (B3), U9.19 (IN3)
unnamed: R39.1, U7.15 (B4), U9.21 (IN4)
unnamed: R28.1, U7.14 (B5), U8.13 (IN1)
unnamed: R29.1, U7.13 (B6), U8.15 (IN2)
unnamed: R30.1, U7.12 (B7), U8.19 (IN3)
unnamed: R31.1, U7.11 (B8), U8.21 (IN4)
